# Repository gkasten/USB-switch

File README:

These scripts work with a USB switcher board to enable automated testing of an
Android device in host mode. They were written as part of Benjamin Fair's
(benjaminfair@) internship during summer 2016. For more information contact his
host Glenn Kasten (gkasten@).

In order to use the scripts in this directory, you must install some
dependencies. These dependencies vary based on which version of the board you
wish to use. See below for more information.

The scripts require a udev rules file to be installed which is included as
"49-ftdi.rules". Install it to "/etc/udev/rules.d/49-ftdi.rules" then run
"udevadm trigger" as root or reboot. The scripts can also be run as root instead
of installing the rules file.

The following kernel drivers/modules may interfere with access to the ftdi
chip on the board and so may have to be unloaded/blacklisted:
        ftdi_sio
        usbserial

usbswitch.py    Supports initial USB switch prototype with an Adafruit FT232H
                GPIO chip. Requires Adafruit_GPIO library from
                https://github.com/adafruit/Adafruit_Python_GPIO

usbswitch2.py   Supports new single-board switch (red PCB). Only requires
                libftdi1-dev which is in most distributions' repos. Could easily
                be ported to C and statically compiled to eliminate all
                dependencies.

adb.sh          Simple wrapper for adb that handles switching to debug mode and
                back to run mode after executing a command.

full.sh         Example script that shows how to use the switch to run tests
                using the WALT device and app in a fully automated way.

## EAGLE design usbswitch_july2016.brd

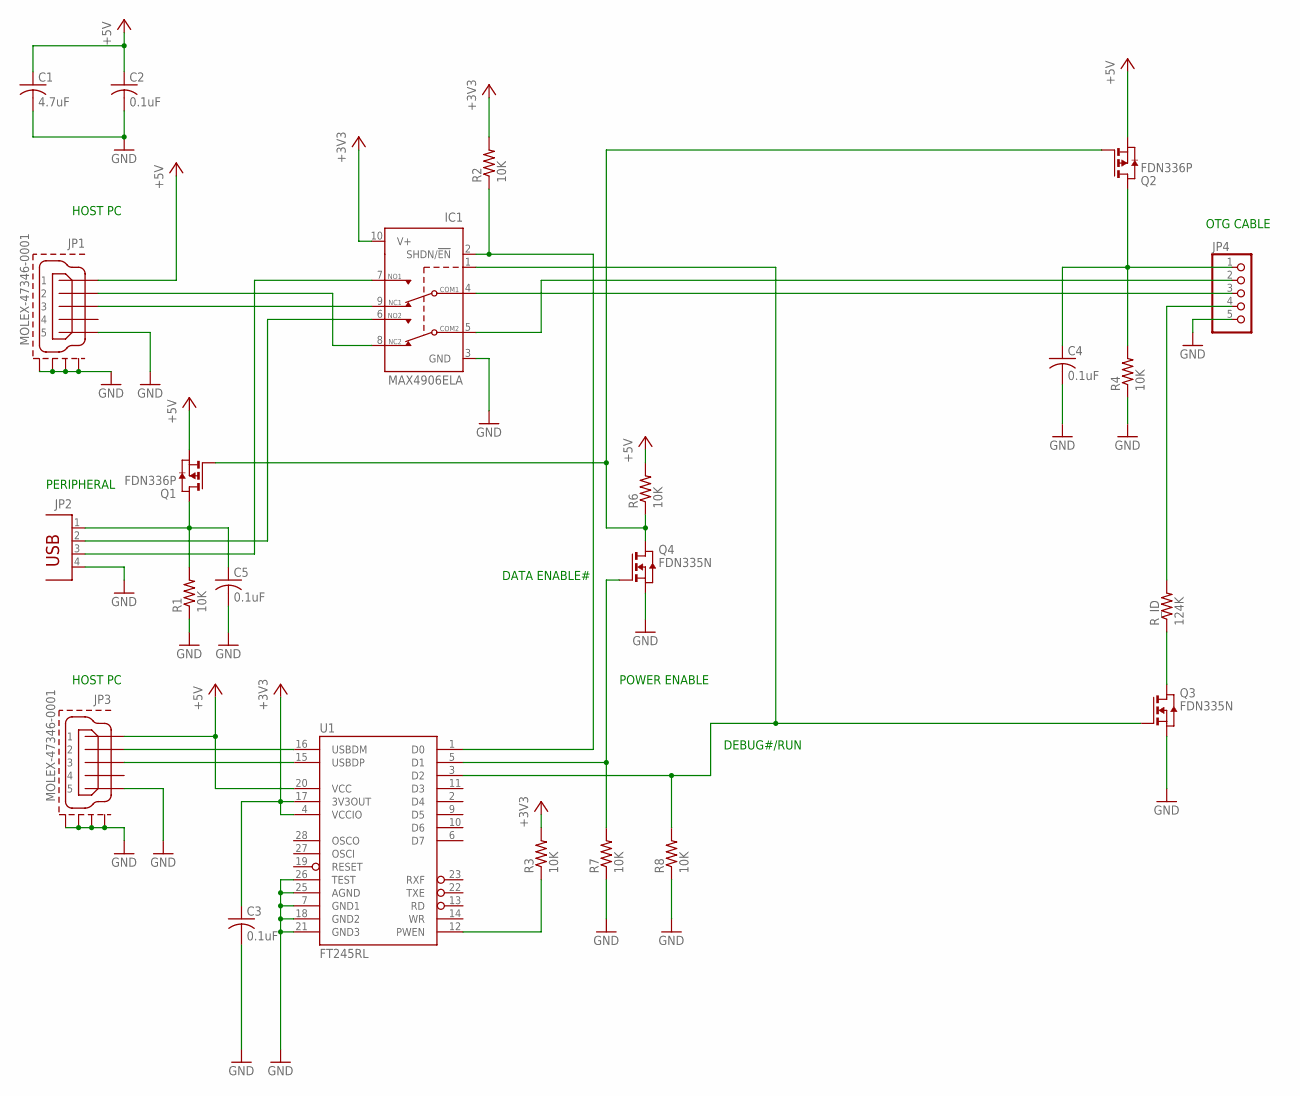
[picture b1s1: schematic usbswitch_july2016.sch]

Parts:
C1: 4.7uF; C1210K
C2, C3, C4, C5: 0.1uF; C0805K
IC1: MAX4906ELA; UDFN10
JP1, JP3: MOLEX-47346-0001; MOLEX-47364-0001
JP2: PN87520
JP4: PINHD-1X5; 1X05
Q1, Q2: FDN336P; SOT-23
Q3, Q4: FDN335N; SOT-23
R1, R2, R3, R4, R6, R7, R8: 10K; R0805W
R_ID: 124K; R0805W
U1: FT245RL; SSOP28DB

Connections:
+3V3: C3.1, IC1.10 (V+), R2.2, R3.2, U1.4 (VCCIO), U1.17 (3V3OUT)
+5V: C1.1, C2.1, JP1.1, JP3.1, Q1.2 (S), Q2.2 (S), R6.2, U1.20 (VCC)
GND: C1.2, C2.2, C3.2, C4.2, C5.2, IC1.3 (GND), JP1.5, JP1.GND1, JP1.GND2, JP1.GND3, JP1.GND4, JP2.4, JP3.5, JP3.GND1, JP3.GND2, JP3.GND3, JP3.GND4, JP4.5, Q3.2 (S), Q4.2 (S), R1.1, R4.1, R7.1, R8.1, U1.7 (GND1), U1.18 (GND2), U1.21 (GND3), U1.25 (AGND), U1.26 (TEST)
unnamed: IC1.4 (COM1), JP4.3
unnamed: IC1.2 (SHDN/!EN), R2.1, U1.1 (D0)
unnamed: C5.1, JP2.1, Q1.1 (D), R1.2
unnamed: C4.1, JP4.1, Q2.1 (D), R4.2
unnamed: IC1.9 (NC1), JP1.3
unnamed: IC1.8 (NC2), JP1.2
unnamed: Q3.1 (D), R_ID.1
unnamed: Q4.3 (G), R7.2, U1.5 (D1)
unnamed: IC1.6 (NO2), JP2.2
unnamed: IC1.7 (NO1), JP2.3
unnamed: JP3.2, U1.16 (USBDM)
unnamed: IC1.1 (IN), Q3.3 (G), R8.2, U1.3 (D2)
unnamed: Q1.3 (G), Q2.3 (G), Q4.1 (D), R6.1
unnamed: R3.1, U1.12 (PWEN)
unnamed: JP4.4, R_ID.2
unnamed: IC1.5 (COM2), JP4.2
unnamed: JP3.3, U1.15 (USBDP)

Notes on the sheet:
PERIPHERAL
OTG CABLE
HOST PC
DATA ENABLE#
DEBUG#/RUN
POWER ENABLE

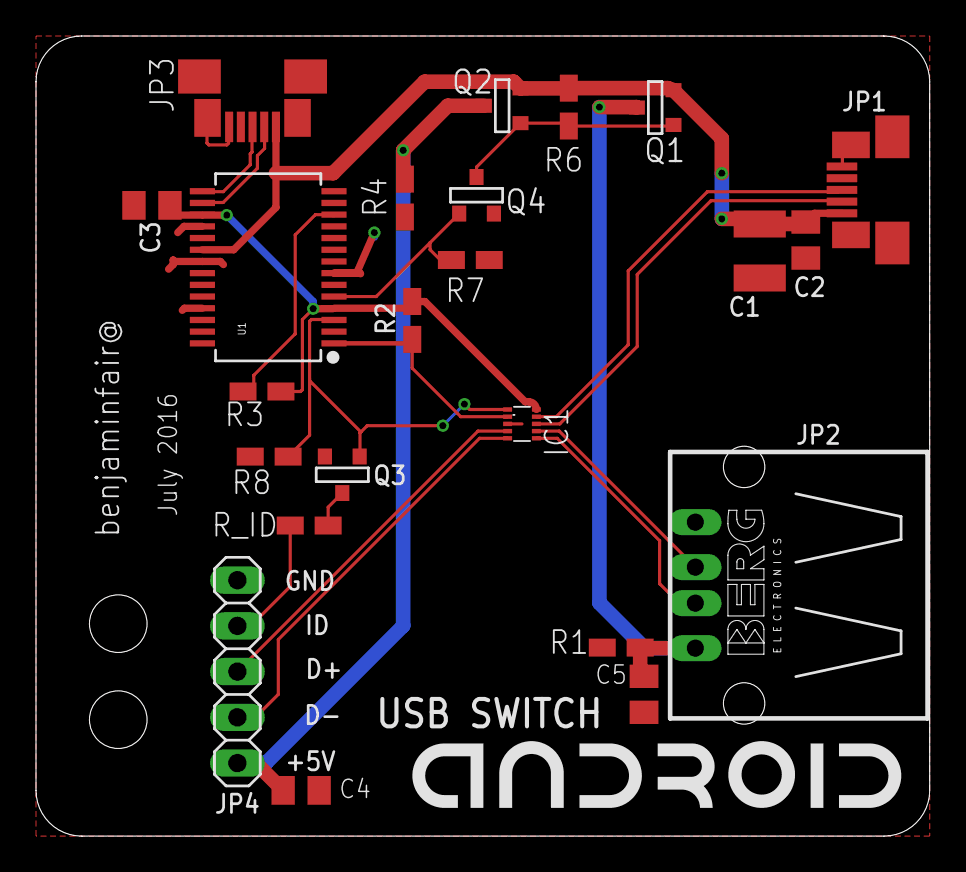
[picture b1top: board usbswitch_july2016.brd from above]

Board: 2 copper layers, 49.6 x 44.5 mm, 24 parts (0 on the bottom side), 20 nets.

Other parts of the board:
U$1: ANDROID_MARK_25

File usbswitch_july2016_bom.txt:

Partlist exported from /usr/local/google/home/benjaminfair/eagle/usbswitch2/usbswitch_july2016.sch at 8/1/16 6:14 PM

Part Value            Device           Package          Description                       MF MPN OC_FARNELL OC_NEWARK
C1   4.7uF            C-USC1210K       C1210K           CAPACITOR, American symbol                                   
C2   0.1uF            C-USC0805K       C0805K           CAPACITOR, American symbol                                   
C3   0.1uF            C-USC0805K       C0805K           CAPACITOR, American symbol                                   
C4   0.1uF            C-USC0805K       C0805K           CAPACITOR, American symbol                                   
C5   0.1uF            C-USC0805K       C0805K           CAPACITOR, American symbol                                   
IC1  MAX4906ELA       MAX4906ELA       UDFN10           High-/Full-Speed USB 2.0 Switches        unknown    unknown  
JP1  MOLEX-47346-0001 MOLEX-47346-0001 MOLEX-47364-0001 MICRO USB B, BOTTOM MOUNT                                    
JP2                   PN87520          PN87520          BERG USB connector                       unknown    unknown  
JP3  MOLEX-47346-0001 MOLEX-47346-0001 MOLEX-47364-0001 MICRO USB B, BOTTOM MOUNT                                    
JP4                   PINHD-1X5        1X05             PIN HEADER                                                   
Q1   FDN336P          PMOSSOT23        SOT-23           MOS FET                                  unknown    unknown  
Q2   FDN336P          PMOSSOT23        SOT-23           MOS FET                                  unknown    unknown  
Q3   FDN335N          NMOSSTO23        SOT-23           MOS FET                                                      
Q4   FDN335N          NMOSSTO23        SOT-23           MOS FET                                                      
R1   10K              R-US_R0805W      R0805W           RESISTOR, American symbol                                    
R2   10K              R-US_R0805W      R0805W           RESISTOR, American symbol                                    
R3   10K              R-US_R0805W      R0805W           RESISTOR, American symbol                                    
R4   10K              R-US_R0805W      R0805W           RESISTOR, American symbol                                    
R6   10K              R-US_R0805W      R0805W           RESISTOR, American symbol                                    
R7   10K              R-US_R0805W      R0805W           RESISTOR, American symbol                                    
R8   10K              R-US_R0805W      R0805W           RESISTOR, American symbol                                    
R_ID 124K             R-US_R0805W      R0805W           RESISTOR, American symbol                                    
U1   FT245RL          FT245RL          SSOP28DB         USB FIFO Controller

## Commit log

2016-09-02 Initial commit from 0c3bb2f3dab56ccb054b3cceca84b4b7df35fee0
2016-09-02 Add part list
2017-08-16 Remove link to confidential document

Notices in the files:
parts and their libraries:
SparkFun-DigitalIC: Licensing: Creative Commons ShareAlike 4.0 International - https://creativecommons.org/licenses/by-sa/4.0
